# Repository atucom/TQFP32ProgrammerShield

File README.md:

# TQFP32 Programmer Shield

This repository contains the Eagle files containing the schematic and PCB board design for a custom designed Arduino Shield. This Arduino Shield is meant to simple be a programmer for the TQFP32 package Atmega328PAU chips. The TQFP32 to DIP adapters are easily found on ebay.

## Bill of Materials:
 * 1x 16Mhz Crystal
 * 2x strips of .1" pitch male headers
 * 2x strips of .1" pitch female headers
 * 2x 22pF ceramic caps
 * 1x 220 ohm resistor
 * 1x TQFP32 to DIP adapter

## Pictures:
 * 
 * 
 * 

## Programming:
Programming the inserted TQFP32 Atmega is the same as programming any other non flashed single chip.
 * Flash your Arduino Uno with the ArduinoISP sketch
 * Upload your actual sketch using Sketch > Upload Using Programmer

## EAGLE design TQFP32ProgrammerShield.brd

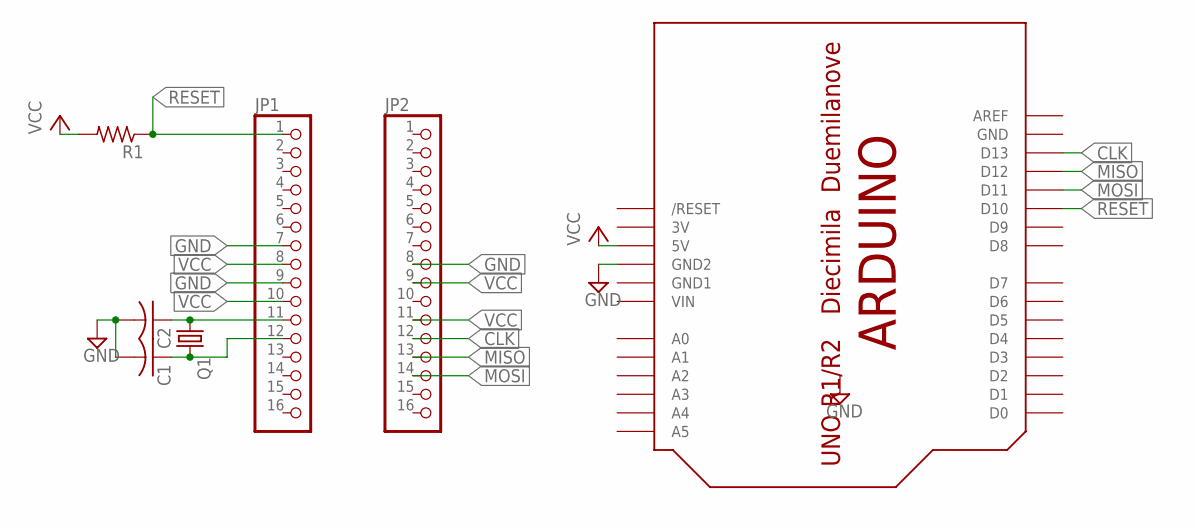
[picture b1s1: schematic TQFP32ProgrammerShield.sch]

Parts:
C1, C2: C-US025-030X050; C025-030X050
JP1, JP2: PINHD-1X16; 1X16
Q1: CRYSTALHC49S; HC49/S
R1: R-US_0204/7; 0204/7
U$1: ARDUINO-NODIM

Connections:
3V: U$1.3V
CLK: JP2.12, U$1.D13
CLK2: C1.1, JP1.12, Q1.2
GND: C1.2, C2.2, JP1.7, JP1.9, JP2.8, U$1.GND, U$1.GND2
GND1: U$1.GND1
MISO: JP2.13, U$1.D12
MOSI: JP2.14, U$1.D11
unnamed: C2.1, JP1.11, Q1.1
RESET: JP1.1, R1.1, U$1.D10
VCC: JP1.8, JP1.10, JP2.9, JP2.11, R1.2, U$1.5V
VIN: U$1.VIN

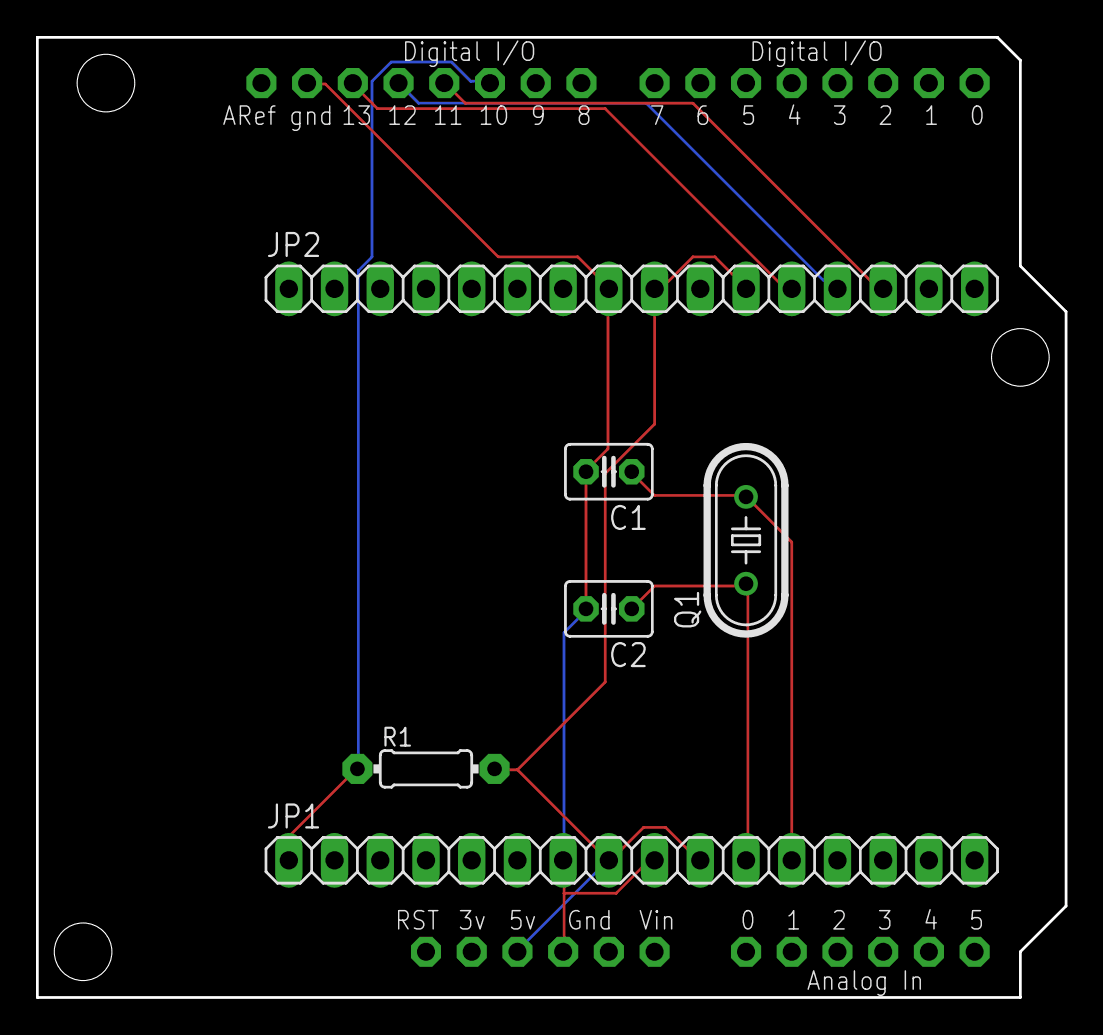
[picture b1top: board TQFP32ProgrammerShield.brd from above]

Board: 2 copper layers, 57.1 x 53.3 mm, 7 parts (0 on the bottom side), 8 nets.

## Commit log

2017-07-17 adding to github
2017-07-17 better photo of assembled board
